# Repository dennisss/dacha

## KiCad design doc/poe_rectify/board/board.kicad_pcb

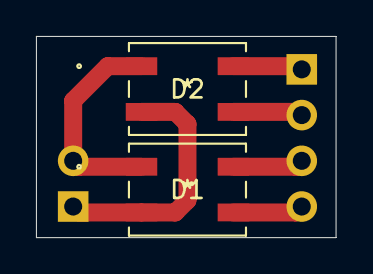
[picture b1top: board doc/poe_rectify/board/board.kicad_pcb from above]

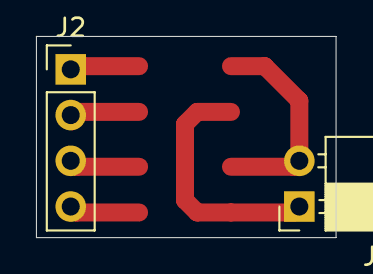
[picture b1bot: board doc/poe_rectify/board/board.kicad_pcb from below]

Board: 2 copper layers, 16.6 x 11.2 mm, 4 parts (2 on the bottom side), 6 nets.

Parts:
D1, D2: D_Bridge_+AA-; CD-HD2004
J1: Conn_01x02; PinSocket_1x02_P2.54mm_Horizontal
J2: Conn_01x04; PinHeader_1x04_P2.54mm_Vertical

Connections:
unnamed: D1.2, J2.3
unnamed: D1.3, J2.4
unnamed: D2.2, J2.1
unnamed: D2.3, J2.2
POE+: D1.1, D2.1, J1.2
POE-: D1.4, D2.4, J1.1

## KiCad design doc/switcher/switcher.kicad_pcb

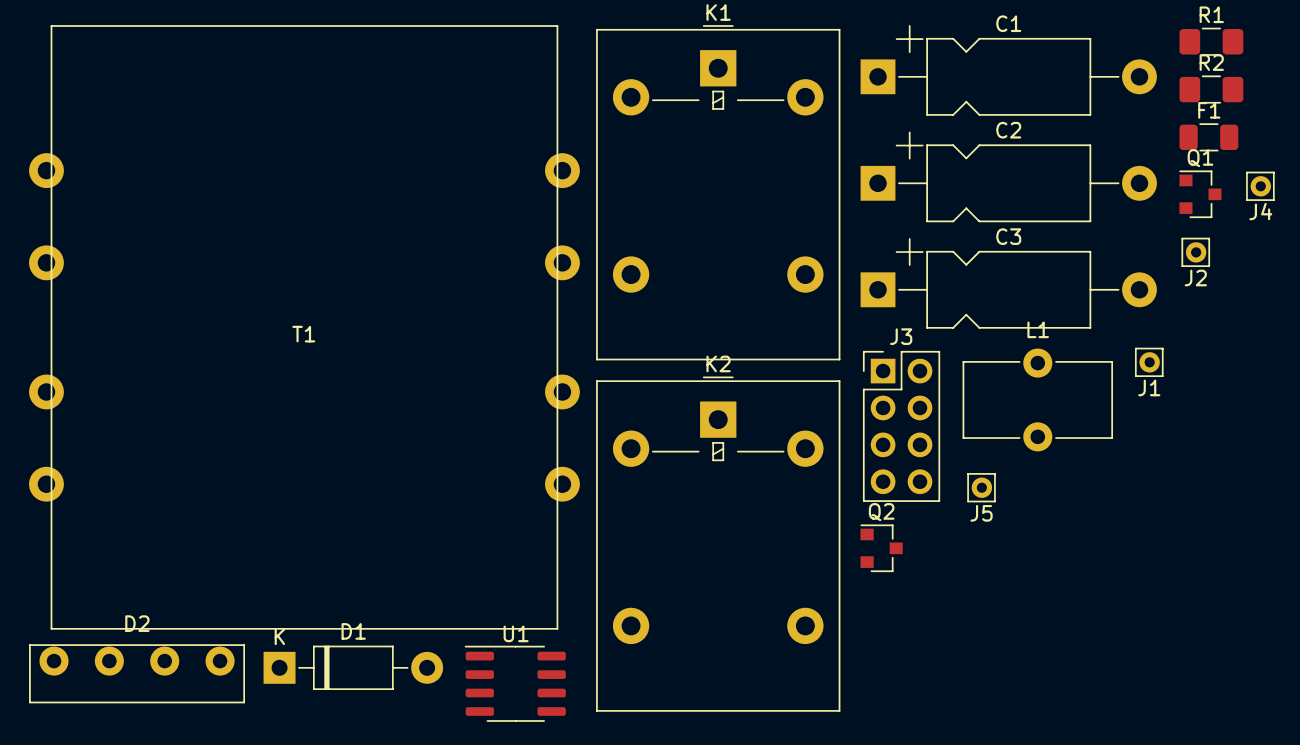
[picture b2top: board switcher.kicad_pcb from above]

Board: 2 copper layers, 20 parts (0 on the bottom side), 16 nets, no tracks yet.

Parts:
C1, C2, C3: CP_Small; CP_Axial_L11.0mm_D5.0mm_P18.00mm_Horizontal
D1: 1N5817; D_DO-41_SOD81_P10.16mm_Horizontal
D2: D_Bridge_+AA-; KBP210G
F1: Fuse; Fuse_1206_3216Metric
J1: IN1+; Pin_D0.7mm_L6.5mm_W1.8mm_FlatFork
J2: IN2+; Pin_D0.7mm_L6.5mm_W1.8mm_FlatFork
J3: ESP8266; PinHeader_2x04_P2.54mm_Vertical
J4: IN1-; Pin_D0.7mm_L6.5mm_W1.8mm_FlatFork
J5: IN2-; Pin_D0.7mm_L6.5mm_W1.8mm_FlatFork
K1, K2: G5LE-1; Relay_SPDT_Omron-G5LE-1
L1: 150uH; L_Toroid_Vertical_L10.0mm_W5.0mm_P5.08mm
Q1, Q2: BSS138; SOT-23
R1, R2: 10K; R_1206_3216Metric_Pad1.42x1.75mm_HandSolder
T1: 3FD-424
U1: LM2594HVM-3.3; SOIC-8_3.9x4.9mm_P1.27mm

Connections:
+3V3: C2.1, J3.3, J3.7, L1.2, U1.4
+12V: C1.1, C3.1, D2.1, K1.5, K2.5, U1.7
GND: C1.2, C2.2, C3.2, D1.2, D2.4, J3.2, Q1.2, Q2.2, R1.2, R2.2, U1.5, U1.6
GPIO0: J3.6, Q2.1, R2.1
GPIO2: J3.4, Q1.1, R1.1
unnamed: D1.1, L1.1, U1.8
unnamed: D2.2, T1.5, T1.7
unnamed: D2.3, T1.6, T1.8
unnamed: F1.1, T1.1, T1.3
unnamed: J1.1, K1.1
unnamed: J2.1, K2.1
unnamed: J4.1, K1.3
unnamed: J5.1, K2.3
unnamed: K1.2, Q1.3
unnamed: K2.2, Q2.3
VAC-: T1.2, T1.4

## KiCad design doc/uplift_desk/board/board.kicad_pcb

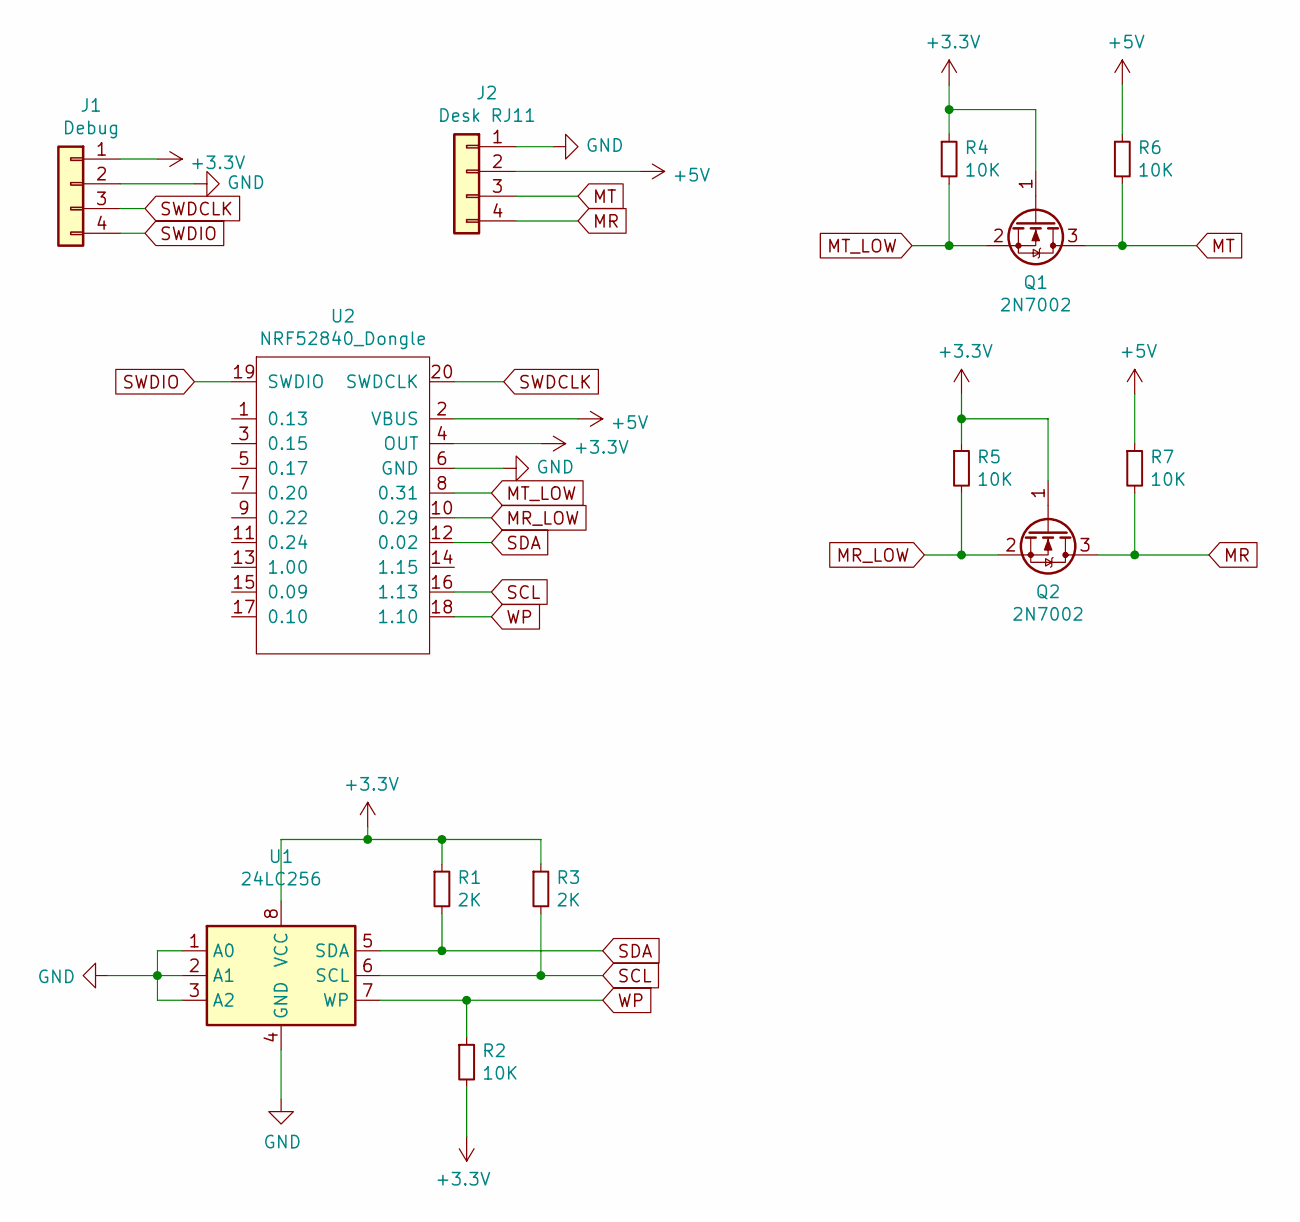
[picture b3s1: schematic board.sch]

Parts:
J1: Debug; PinHeader_1x04_P2.54mm_Horizontal
J2: Desk RJ11; PinHeader_1x04_P2.54mm_Vertical
Q1, Q2: 2N7002; SOT-23
R1, R3: 2K; R_0805_2012Metric_Pad1.15x1.40mm_HandSolder
R2, R4, R5, R6, R7: 10K; R_0805_2012Metric_Pad1.15x1.40mm_HandSolder
U1: 24LC256; DIP-8_W7.62mm_LongPads
U2: NRF52840_Dongle

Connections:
+3V3: J1.1, Q1.1 (G), Q2.1 (G), R1.1, R2.2, R3.1, R4.1, R5.1, U1.8 (VCC), U2.4 (OUT)
+5V: J2.2, R6.1, R7.1, U2.2 (VBUS)
GND: J1.2, J2.1, U1.1 (A0), U1.2 (A1), U1.3 (A2), U1.4 (GND), U2.6 (GND)
MR: J2.4, Q2.3 (D), R7.2
MR_LOW: Q2.2 (S), R5.2, U2.10 (0.29)
MT: J2.3, Q1.3 (D), R6.2
MT_LOW: Q1.2 (S), R4.2, U2.8 (0.31)
SCL: R3.2, U1.6 (SCL), U2.16 (1.13)
SDA: R1.2, U1.5 (SDA), U2.12 (0.02)
SWDCLK: J1.3, U2.20 (SWDCLK)
SWDIO: J1.4, U2.19 (SWDIO)
WP: R2.1, U1.7 (WP), U2.18 (1.10)

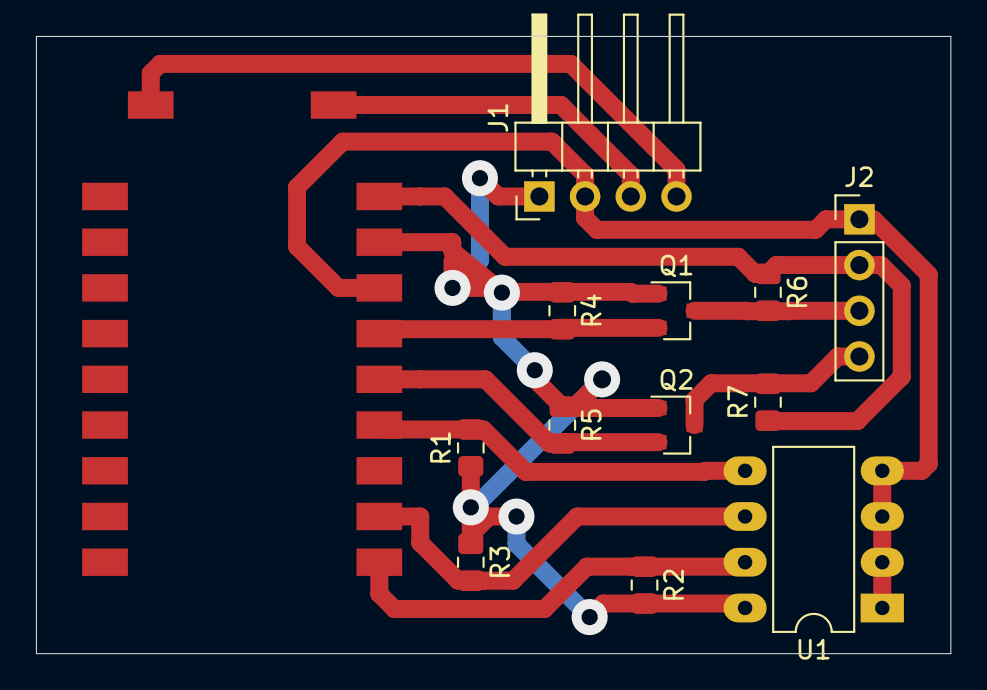
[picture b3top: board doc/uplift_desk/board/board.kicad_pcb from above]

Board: 2 copper layers, 50.8 x 34.3 mm, 13 parts (0 on the bottom side), 12 nets.

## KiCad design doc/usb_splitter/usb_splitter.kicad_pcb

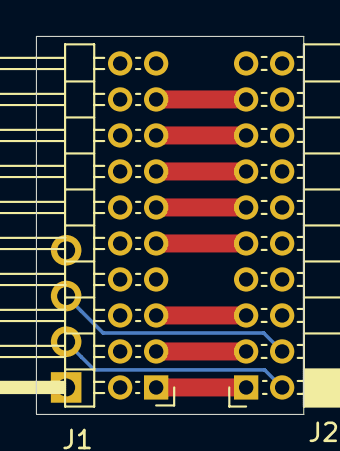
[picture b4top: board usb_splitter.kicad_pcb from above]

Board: 4 copper layers, 14.8 x 21.0 mm, 3 parts (1 on the bottom side), 11 nets.

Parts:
J1: FPANEL_USB3; PinHeader_2x10_P2.00mm_Horizontal
J2: MOTHERBOARD; PinSocket_2x10_P2.00mm_Horizontal
J3: FPANEL_USB2; PinSocket_1x04_P2.54mm_Horizontal

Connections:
GND: J1.7, J1.13, J2.6, J2.7, J2.12, J2.13, J3.1
ID: J1.1, J2.1
USB1_D+: J1.3, J2.3
USB1_D-: J1.5, J2.5
USB1_SSRX+: J1.15, J2.15
USB1_SSRX-: J1.17, J2.17
USB1_SSTX+: J1.9, J2.9
USB1_SSTX-: J1.11, J2.11
USB2_D+: J2.2, J3.2
USB2_D-: J2.4, J3.3
VBUS: J1.19, J2.18, J2.19, J3.4

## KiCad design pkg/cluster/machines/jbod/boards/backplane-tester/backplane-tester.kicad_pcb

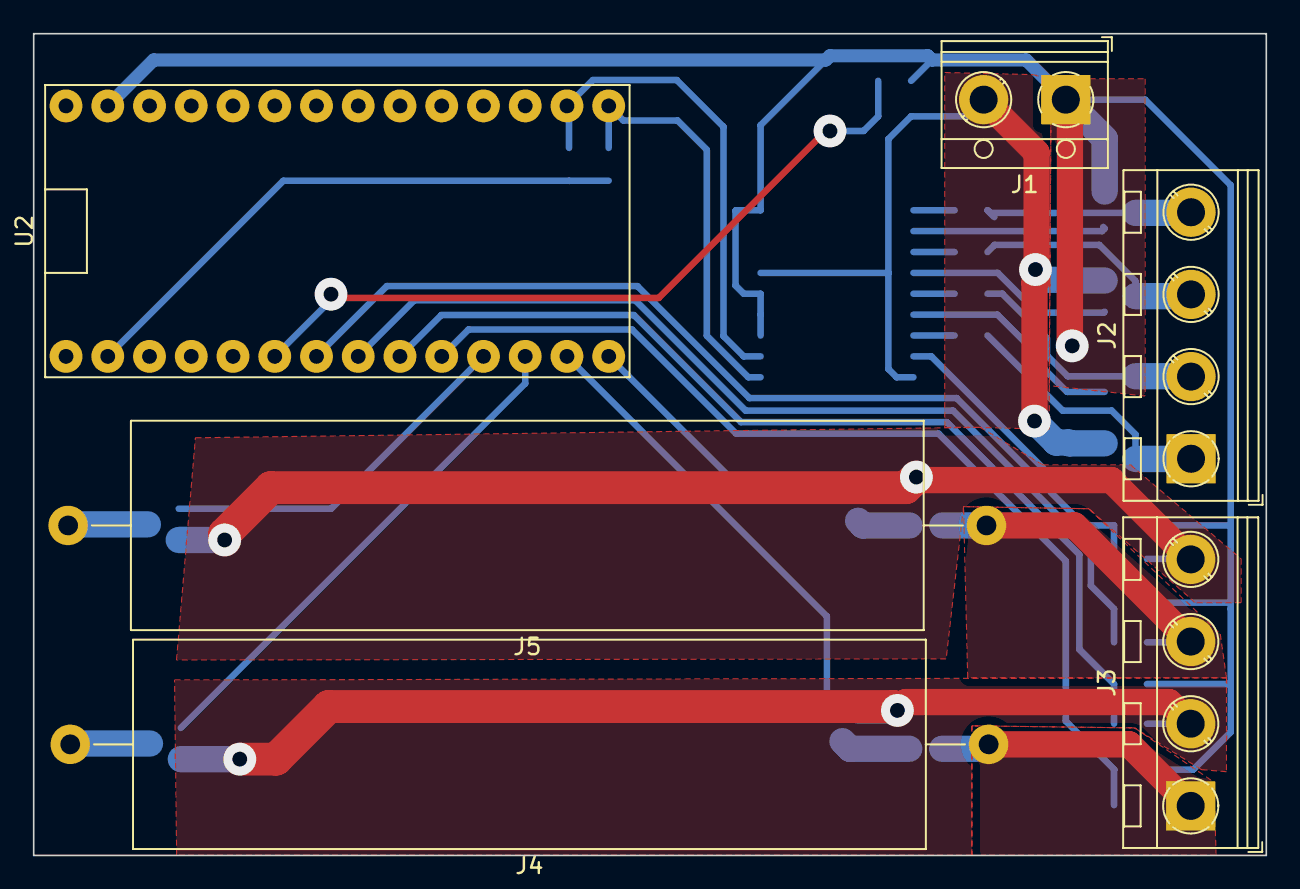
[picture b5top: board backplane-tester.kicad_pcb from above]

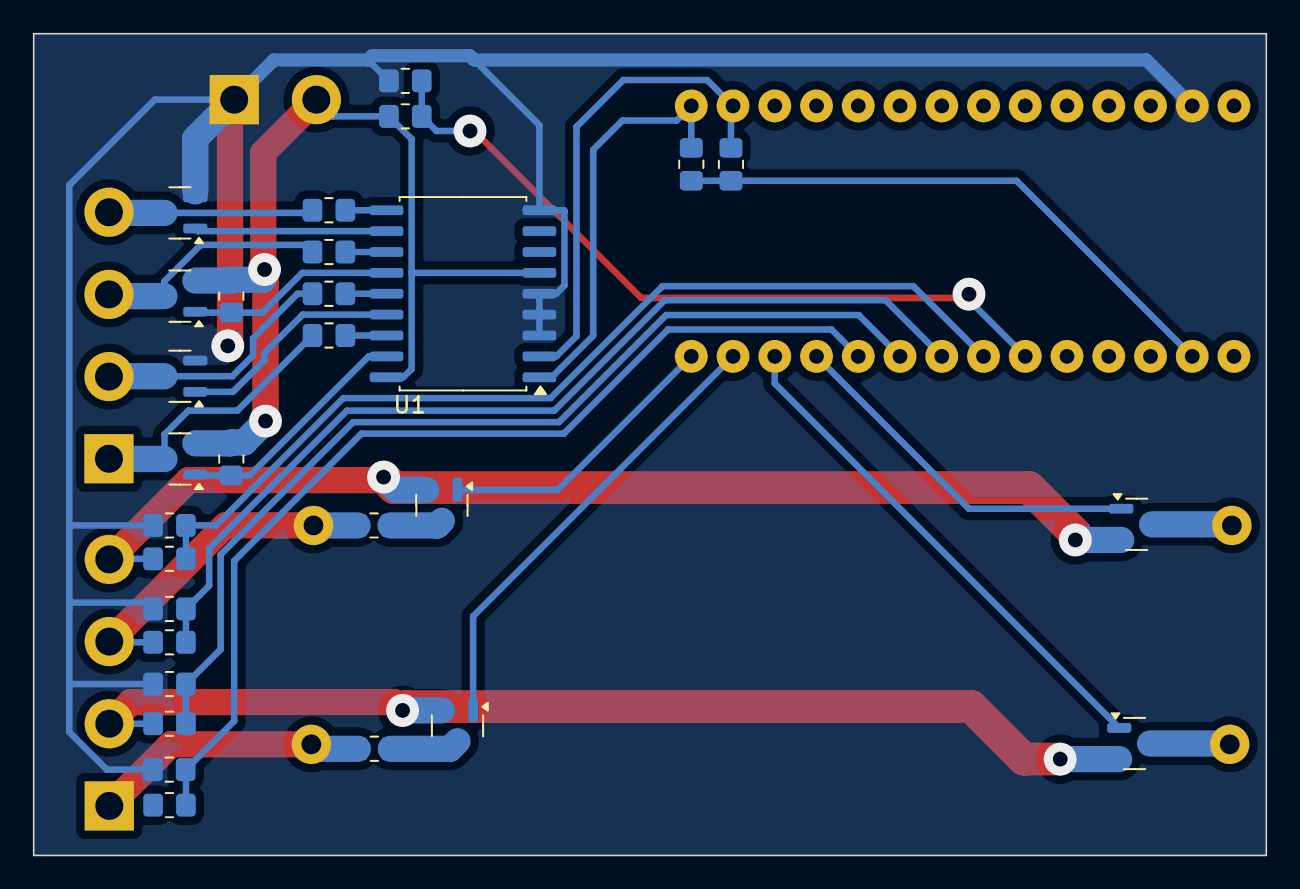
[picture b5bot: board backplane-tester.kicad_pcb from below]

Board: 2 copper layers, 75.0 x 50.0 mm, 35 parts (29 on the bottom side), 34 nets.

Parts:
J1: POWER; TerminalBlock_RND_205-00012_1x02_P5.00mm_Horizontal
J2: BOARD_IN; TerminalBlock_RND_205-00047_1x04_P5.00mm_Horizontal
J3: SAS_OUT; TerminalBlock_RND_205-00047_1x04_P5.00mm_Horizontal
J4: POWER_RES1; R_Axial_Power_L48.0mm_W12.5mm_P55.88mm
J5: POWER_RES2; R_Axial_Power_L48.0mm_W12.5mm_P55.88mm
Q1, Q4, Q5, Q6, Q8, Q9: DMG2302U; SOT-23
Q2, Q3: DMG2305_P; SOT-23
R1, R2, R3, R8, R9, R10, R11, R12, R13, R14, R23, R24: 10K; R_0805_2012Metric_Pad1.20x1.40mm_HandSolder
R4, R5, R6, R7: 1K; R_0805_2012Metric_Pad1.20x1.40mm_HandSolder
R19, R20: 4.7K; R_0805_2012Metric_Pad1.20x1.40mm_HandSolder
R21, R22: 470; R_0805_2012Metric_Pad1.20x1.40mm_HandSolder
U1: MCP23008-xSO; SOIC-18W_7.5x11.6mm_P1.27mm
U2: NRF52840_ITSY_BITSY

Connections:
5V_SENSE: R2.2, R3.1, U2.6 (A1/P0.30)
+3.3V: R19.2, R20.2, U2.2 (3V3)
+5V: J1.2, Q2.2 (S), Q3.2 (S), R1.1, R2.1, R9.1, U1.6 (~RESET), U1.18 (VDD)
BOARD_IN_GND1: J2.2, Q1.3 (D), R6.2
BOARD_IN_GND1_CTRL: Q1.1 (G), U1.15 (GP5)
BOARD_IN_GND2: J2.4, Q4.3 (D), R4.2
BOARD_IN_GND2_CTRL: Q4.1 (G), U1.11 (GP1)
BOARD_IN_V1: J2.1, Q2.3 (D), R7.2
BOARD_IN_V1_CTRL_5V: Q2.1 (G), R1.2, U1.17 (GP7)
BOARD_IN_V2: J2.3, Q3.3 (D), R5.2
BOARD_IN_V2_CTRL_5V: Q3.1 (G), R9.2, U1.13 (GP3)
GND: J1.1, Q1.2 (S), Q4.2 (S), R3.2, R10.2, R12.2, R14.2, R24.2, U1.3 (A2), U1.4 (A1), U1.5 (A0), U1.9 (VSS), U2.27 (GND)
unnamed: J4.2, Q5.3 (D)
unnamed: J5.2, Q6.3 (D)
unnamed: Q8.3 (D), R21.1
unnamed: Q9.3 (D), R22.1
unnamed: R4.1, U1.10 (GP0)
unnamed: R5.1, U1.12 (GP2)
unnamed: R6.1, U1.14 (GP4)
unnamed: R7.1, U1.16 (GP6)
POWER_RES1S_CTRL: Q8.1 (G), U2.13 (MISO/P0.20)
POWER_RES1_CTRL: Q5.1 (G), U2.12 (MOSI/P0.15)
POWER_RES2S_CTRL: Q9.1 (G), U2.14 (D2/P1.02)
POWER_RES2_CTRL: Q6.1 (G), U2.11 (SCK/P0.13)
SAS_GND1: J3.2, Q5.2 (S), Q8.2 (S), R8.1
SAS_GND1_SENSE: R8.2, R10.1, U2.9 (A4/P0.02)
SAS_GND2: J3.4, Q6.2 (S), Q9.2 (S), R23.1
SAS_GND2_SENSE: R23.2, R24.1, U2.7 (A2/P0.28)
SAS_V1: J3.1, J4.1, R11.1, R21.2
SAS_V1_SENSE: R11.2, R12.1, U2.10 (A5/P0.03)
SAS_V2: J3.3, J5.1, R13.1, R22.2
SAS_V2_SENSE: R13.2, R14.1, U2.8 (A3/P0.31)
SCL: R19.1, U1.2 (SDA), U2.16 (D1/P0.24)
SDA: R20.1, U1.1 (SCL), U2.15 (D0/P0.25)

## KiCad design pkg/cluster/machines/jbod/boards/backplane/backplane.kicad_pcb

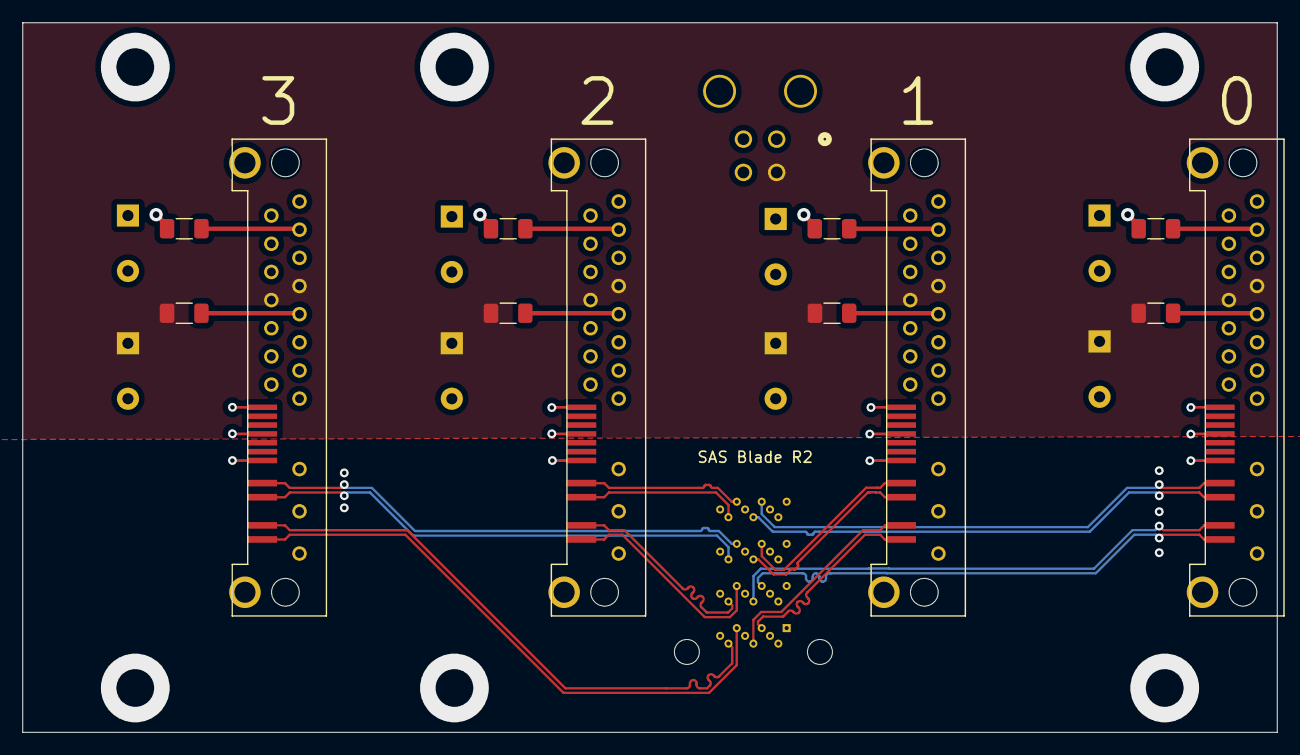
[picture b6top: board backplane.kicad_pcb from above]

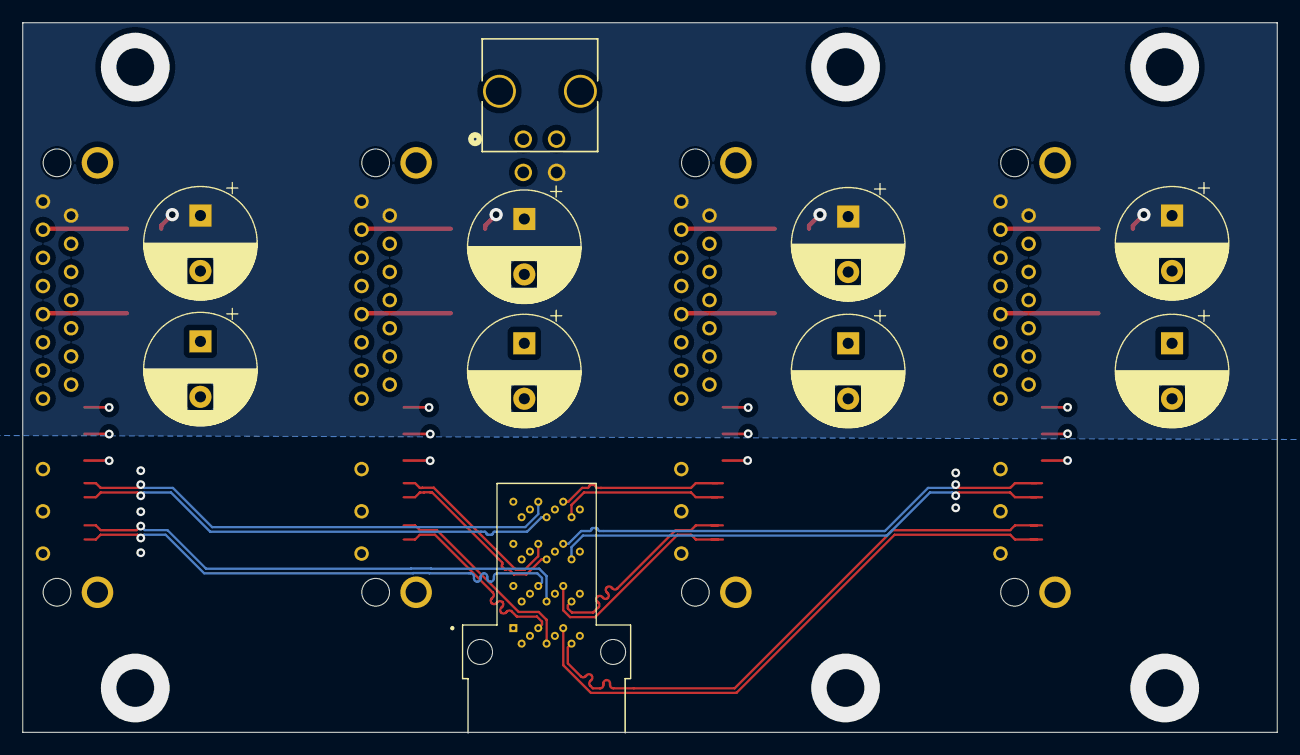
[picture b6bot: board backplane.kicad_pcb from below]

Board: 4 copper layers, 113.1 x 64.0 mm, 22 parts (10 on the bottom side), 27 nets.

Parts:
C1, C2, C3, C4, C5, C6, C7, C8: 220u; CP_Radial_D10.0mm_P5.00mm
CN1, CN2, CN3, CN4: HDD; 0878390018
J1: POWER; CONN_SD-43045-008_04_MOL
J2: MINI_SAS_HD; AMPHENOL_G40H11331HR
R1, R4, R7, R10: 2R0; R_1206_3216Metric_Pad1.30x1.75mm_HandSolder
R2, R5, R8, R11: 5R1; R_1206_3216Metric_Pad1.30x1.75mm_HandSolder

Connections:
+5V: C1.1, C2.1, C6.1, C8.1, CN1.5V2, CN1.5V3, CN2.5V2, CN2.5V3, CN3.5V2, CN3.5V3, CN4.5V2, CN4.5V3, J1.3, R1.2, R4.2, R7.2, R10.2
+12V: C3.1, C4.1, C5.1, C7.1, CN1.12V2, CN1.12V3, CN2.12V2, CN2.12V3, CN3.12V2, CN3.12V3, CN4.12V2, CN4.12V3, J1.4, R2.2, R5.2, R8.2, R11.2
GND: C1.2, C2.2, C3.2, C4.2, C5.2, C6.2, C7.2, C8.2, CN1.GND1 (GNDP), CN1.GND2 (GNDP), CN1.GND3 (GNDP), CN1.GND4 (GNDS), CN1.GND5 (GNDS), CN1.GND6 (GNDS), CN1.GND7 (GND1), CN1.GND8 (GND2), CN1.GND9 (GND3), CN1.GND10 (GND4), CN1.GND12 (GND6), CN2.GND1 (GNDP), CN2.GND2 (GNDP), CN2.GND3 (GNDP), CN2.GND4 (GNDS), CN2.GND5 (GNDS), CN2.GND6 (GNDS), CN2.GND7 (GND1), CN2.GND8 (GND2), CN2.GND9 (GND3), CN2.GND10 (GND4), CN2.GND12 (GND6), CN3.GND1 (GNDP), CN3.GND2 (GNDP), CN3.GND3 (GNDP), CN3.GND4 (GNDS), CN3.GND5 (GNDS), CN3.GND6 (GNDS), CN3.GND7 (GND1), CN3.GND8 (GND2), CN3.GND9 (GND3), CN3.GND10 (GND4), CN3.GND12 (GND6), CN4.GND1 (GNDP), CN4.GND2 (GNDP), CN4.GND3 (GNDP), CN4.GND4 (GNDS), CN4.GND5 (GNDS), CN4.GND6 (GNDS), CN4.GND7 (GND1), CN4.GND8 (GND2), CN4.GND9 (GND3), CN4.GND10 (GND4), CN4.GND12 (GND6), J1.1, J1.2, J2.A3, J2.A6, J2.A9, J2.B3, J2.B6, J2.B9, J2.C3, J2.C6, J2.C9, J2.D3, J2.D6, J2.D9
unnamed: CN1.5V1, R1.1
unnamed: CN1.12V1, R2.1
unnamed: CN2.5V1, R4.1
unnamed: CN2.12V1, R5.1
unnamed: CN3.5V1, R7.1
unnamed: CN3.12V1, R8.1
unnamed: CN4.5V1, R10.1
unnamed: CN4.12V1, R11.1
RX0+: CN1.RP+, J2.B4
RX0-: CN1.RP-, J2.B5
RX1+: CN2.RP+, J2.A4
RX1-: CN2.RP-, J2.A5
RX2+: CN3.RP+, J2.B7
RX2-: CN3.RP-, J2.B8
RX3+: CN4.RP+, J2.A7
RX3-: CN4.RP-, J2.A8
TX0+: CN1.TP+, J2.D4
TX0-: CN1.TP-, J2.D5
TX1+: CN2.TP+, J2.C4
TX1-: CN2.TP-, J2.C5
TX2+: CN3.TP+, J2.D7
TX2-: CN3.TP-, J2.D8
TX3+: CN4.TP+, J2.C7
TX3-: CN4.TP-, J2.C8

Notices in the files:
parts and their libraries:
Copyright 2021 Accelerated Designs. All rights reserved.
